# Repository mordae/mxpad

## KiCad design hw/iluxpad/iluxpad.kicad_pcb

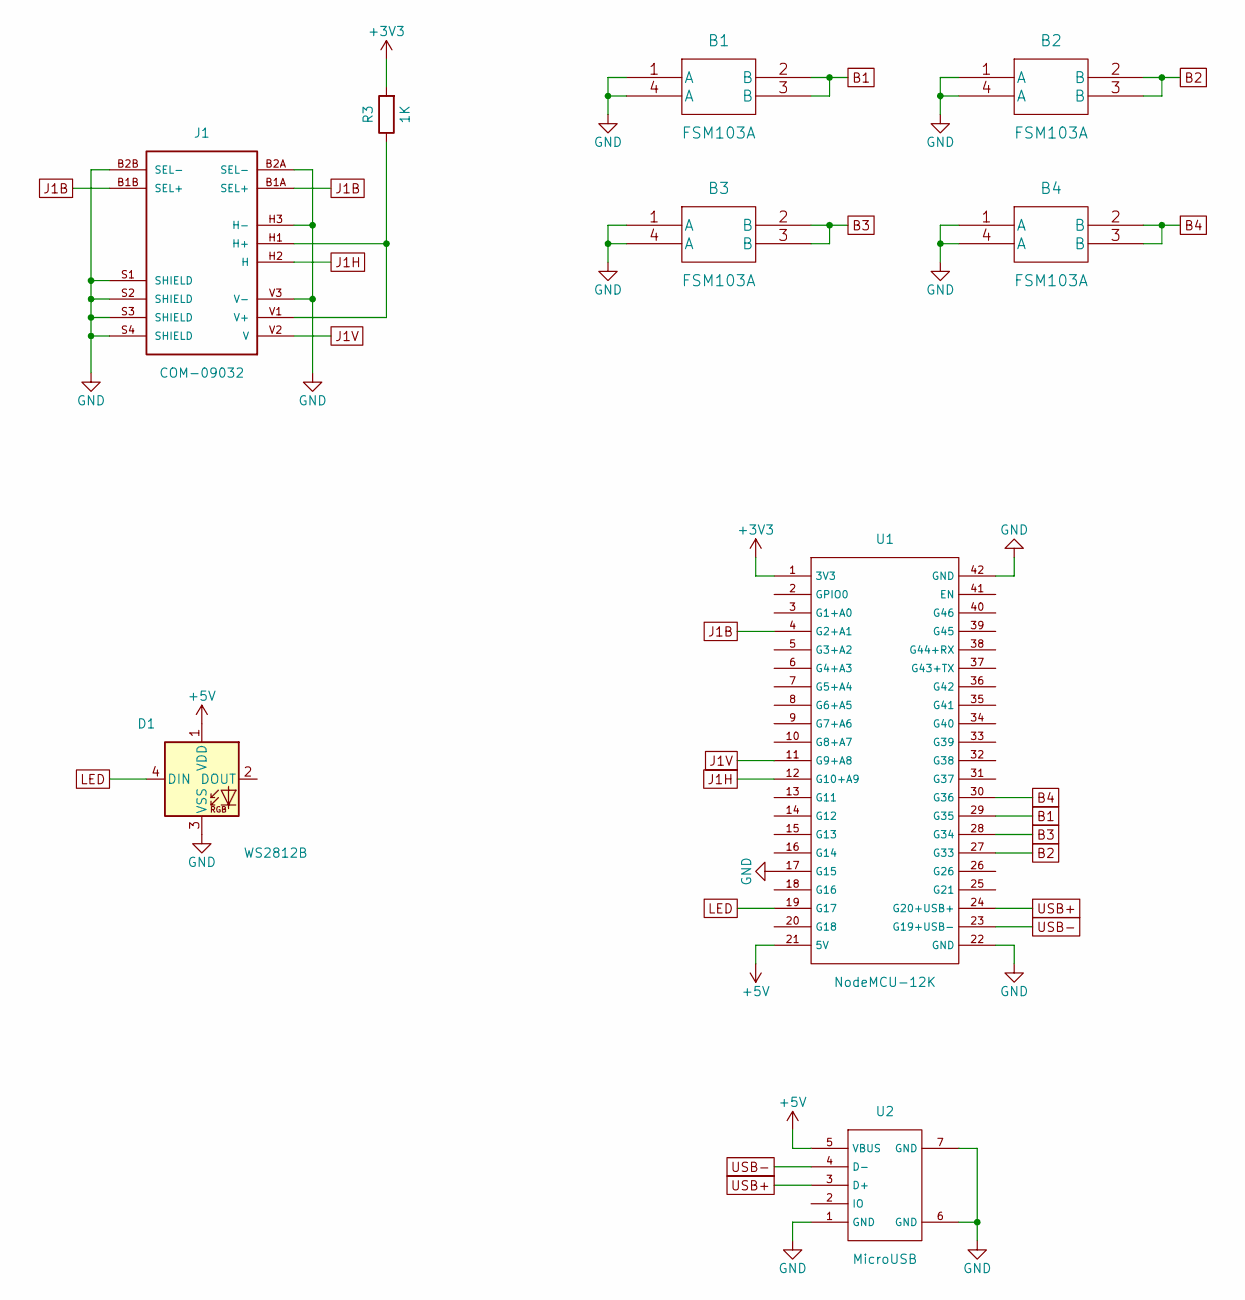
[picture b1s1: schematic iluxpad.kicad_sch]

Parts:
B1, B2, B3, B4: FSM103A; FSM103A-SMD
D1: WS2812B; LED_WS2812B_PLCC4_5.0x5.0mm_P3.2mm
J1: COM-09032; COM-09032-SMD
R3: 1K; R_Axial_DIN0207_L6.3mm_D2.5mm_P10.16mm_Horizontal
U1: NodeMCU-12K; NodeMCU-12K-SMD
U2: MicroUSB

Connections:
+3V3: R3.2, U1.1 (3V3)
+5V: D1.1 (VDD), U1.21 (5V), U2.5 (VBUS)
B1: B1.2 (B), B1.3 (B), U1.29 (G35)
B2: B2.2 (B), B2.3 (B), U1.27 (G33)
B3: B3.2 (B), B3.3 (B), U1.28 (G34)
B4: B4.2 (B), B4.3 (B), U1.30 (G36)
GND: B1.1 (A), B1.4 (A), B2.1 (A), B2.4 (A), B3.1 (A), B3.4 (A), B4.1 (A), B4.4 (A), D1.3 (VSS), J1.B2A (SEL-), J1.B2B (SEL-), J1.H3 (H-), J1.S1 (SHIELD), J1.S2 (SHIELD), J1.S3 (SHIELD), J1.S4 (SHIELD), J1.V3 (V-), U1.17 (G15), U1.22 (GND), U1.42 (GND), U2.1 (GND), U2.6 (GND), U2.7 (GND)
J1B: J1.B1A (SEL+), J1.B1B (SEL+), U1.4 (G2+A1)
J1H: J1.H2 (H), U1.12 (G10+A9)
J1V: J1.V2 (V), U1.11 (G9+A8)
LED: D1.4 (DIN), U1.19 (G17)
unnamed: J1.H1 (H+), J1.V1 (V+), R3.1
USB+: U1.24 (G20+USB+), U2.3 (D+)
USB-: U1.23 (G19+USB-), U2.4 (D-)

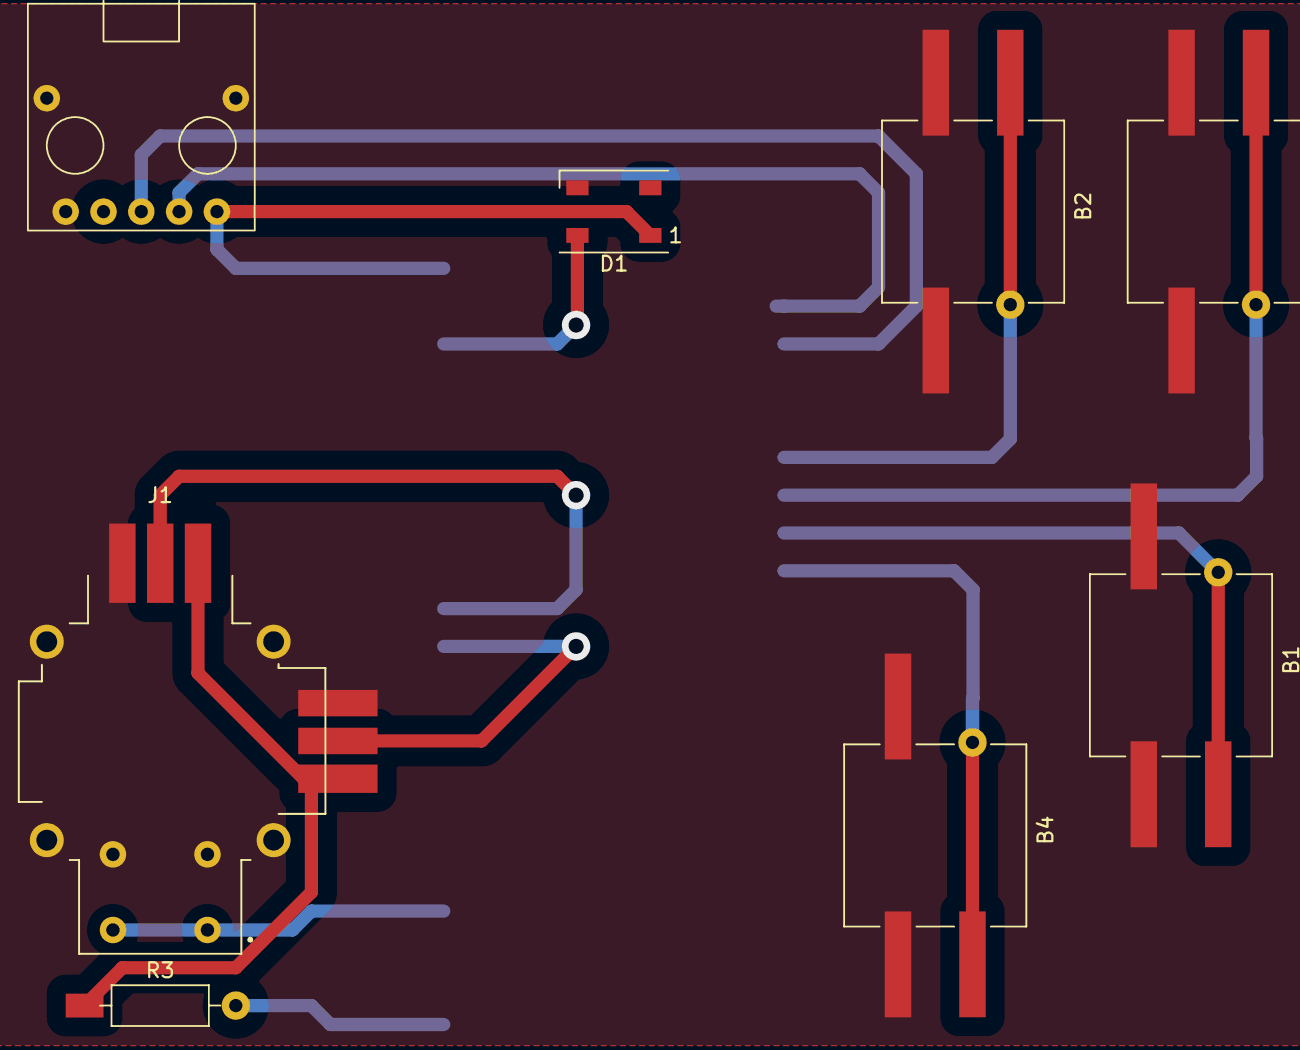
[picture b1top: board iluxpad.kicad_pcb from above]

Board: 2 copper layers, 9 parts (1 on the bottom side), 14 nets.

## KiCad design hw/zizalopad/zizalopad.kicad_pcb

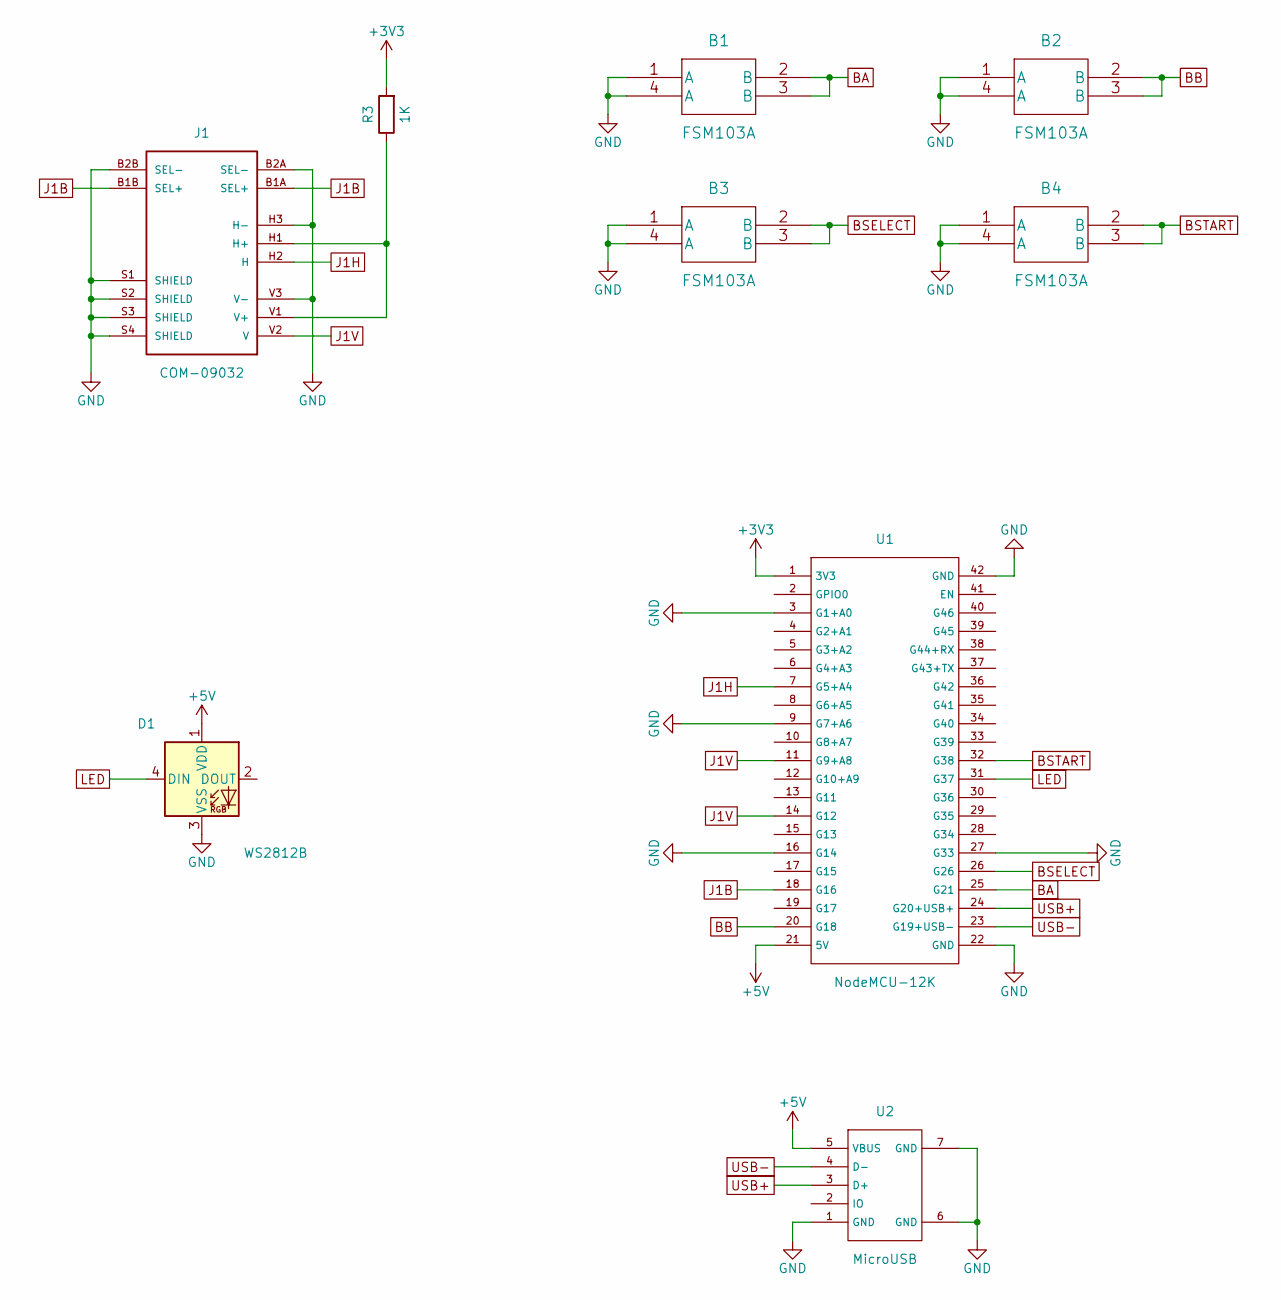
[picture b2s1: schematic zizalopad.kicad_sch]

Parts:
B1, B2, B3, B4: FSM103A; FSM103A-SMD
D1: WS2812B; LED_WS2812B_PLCC4_5.0x5.0mm_P3.2mm
J1: COM-09032; COM-09032-SMD
R3: 1K; R_Axial_DIN0207_L6.3mm_D2.5mm_P7.62mm_Horizontal
U1: NodeMCU-12K; NodeMCU-12K-SMD
U2: MicroUSB

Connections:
+3V3: R3.2, U1.1 (3V3)
+5V: D1.1 (VDD), U1.21 (5V), U2.5 (VBUS)
BA: B1.2 (B), B1.3 (B), U1.25 (G21)
BB: B2.2 (B), B2.3 (B), U1.20 (G18)
BSELECT: B3.2 (B), B3.3 (B), U1.26 (G26)
BSTART: B4.2 (B), B4.3 (B), U1.32 (G38)
GND: B1.1 (A), B1.4 (A), B2.1 (A), B2.4 (A), B3.1 (A), B3.4 (A), B4.1 (A), B4.4 (A), D1.3 (VSS), J1.B2A (SEL-), J1.B2B (SEL-), J1.H3 (H-), J1.S1 (SHIELD), J1.S2 (SHIELD), J1.S3 (SHIELD), J1.S4 (SHIELD), J1.V3 (V-), U1.3 (G1+A0), U1.9 (G7+A6), U1.16 (G14), U1.22 (GND), U1.27 (G33), U1.42 (GND), U2.1 (GND), U2.6 (GND), U2.7 (GND)
J1B: J1.B1A (SEL+), J1.B1B (SEL+), U1.18 (G16)
J1H: J1.H2 (H), U1.7 (G5+A4)
J1V: J1.V2 (V), U1.11 (G9+A8), U1.14 (G12)
LED: D1.4 (DIN), U1.31 (G37)
unnamed: J1.H1 (H+), J1.V1 (V+), R3.1
USB+: U1.24 (G20+USB+), U2.3 (D+)
USB-: U1.23 (G19+USB-), U2.4 (D-)

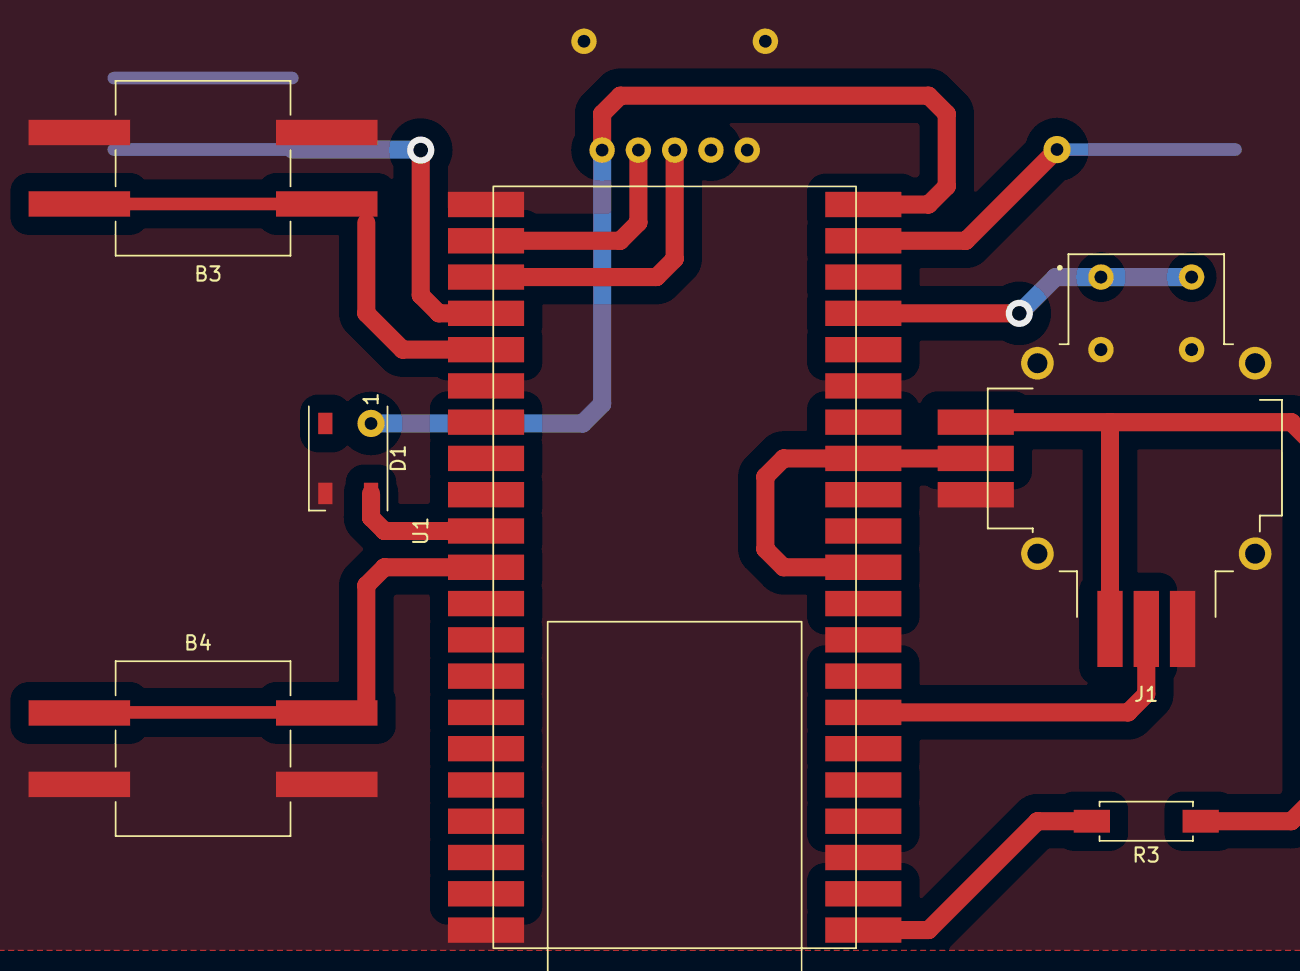
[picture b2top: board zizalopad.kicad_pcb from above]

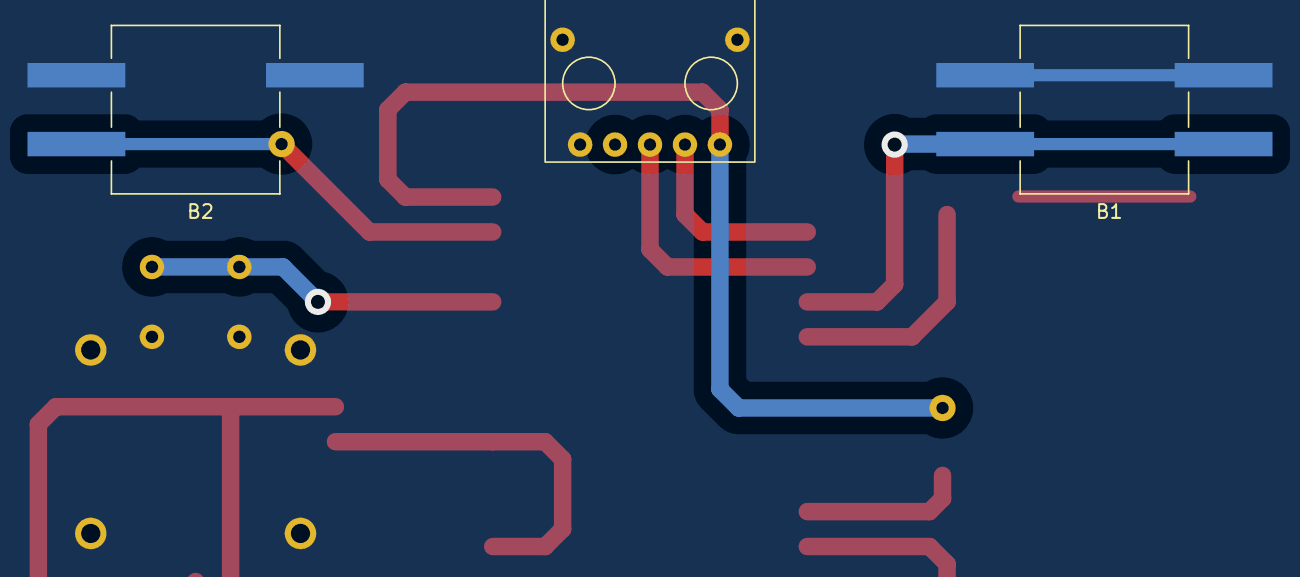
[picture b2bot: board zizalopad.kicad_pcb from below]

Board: 2 copper layers, 9 parts (3 on the bottom side), 14 nets.

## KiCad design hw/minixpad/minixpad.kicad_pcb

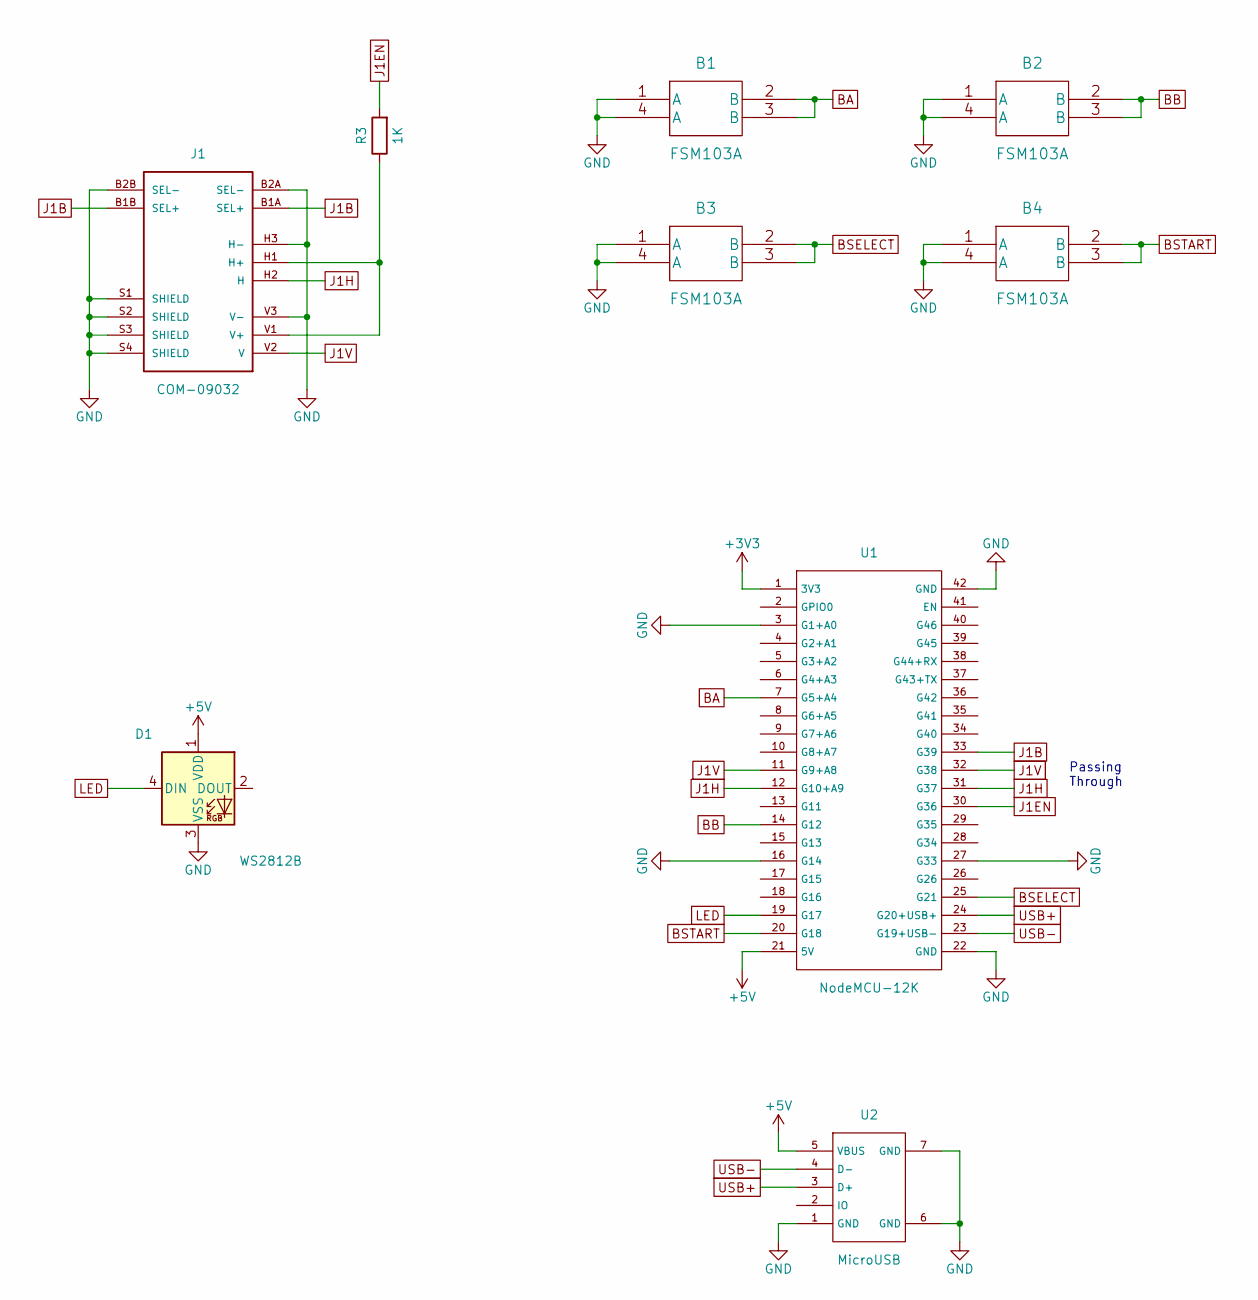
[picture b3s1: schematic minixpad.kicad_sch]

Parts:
B1, B2, B3, B4: FSM103A; FSM103A-SMD
D1: WS2812B; LED_WS2812B_PLCC4_5.0x5.0mm_P3.2mm
J1: COM-09032; COM-09032-SMD
R3: 1K; R_Axial_DIN0204_L3.6mm_D1.6mm_P5.08mm_Horizontal
U1: NodeMCU-12K; NodeMCU-12K-SMD
U2: MicroUSB

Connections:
+3V3: U1.1 (3V3)
+5V: D1.1 (VDD), U1.21 (5V), U2.5 (VBUS)
BA: B1.2 (B), B1.3 (B), U1.7 (G5+A4)
BB: B2.2 (B), B2.3 (B), U1.14 (G12)
BSELECT: B3.2 (B), B3.3 (B), U1.25 (G21)
BSTART: B4.2 (B), B4.3 (B), U1.20 (G18)
GND: B1.1 (A), B1.4 (A), B2.1 (A), B2.4 (A), B3.1 (A), B3.4 (A), B4.1 (A), B4.4 (A), D1.3 (VSS), J1.B2A (SEL-), J1.B2B (SEL-), J1.H3 (H-), J1.S1 (SHIELD), J1.S2 (SHIELD), J1.S3 (SHIELD), J1.S4 (SHIELD), J1.V3 (V-), U1.3 (G1+A0), U1.16 (G14), U1.22 (GND), U1.27 (G33), U1.42 (GND), U2.1 (GND), U2.6 (GND), U2.7 (GND)
J1B: J1.B1A (SEL+), J1.B1B (SEL+), U1.33 (G39)
J1EN: R3.2, U1.30 (G36)
J1H: J1.H2 (H), U1.12 (G10+A9), U1.31 (G37)
J1V: J1.V2 (V), U1.11 (G9+A8), U1.32 (G38)
LED: D1.4 (DIN), U1.19 (G17)
unnamed: J1.H1 (H+), J1.V1 (V+), R3.1
USB+: U1.24 (G20+USB+), U2.3 (D+)
USB-: U1.23 (G19+USB-), U2.4 (D-)

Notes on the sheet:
Passing Through

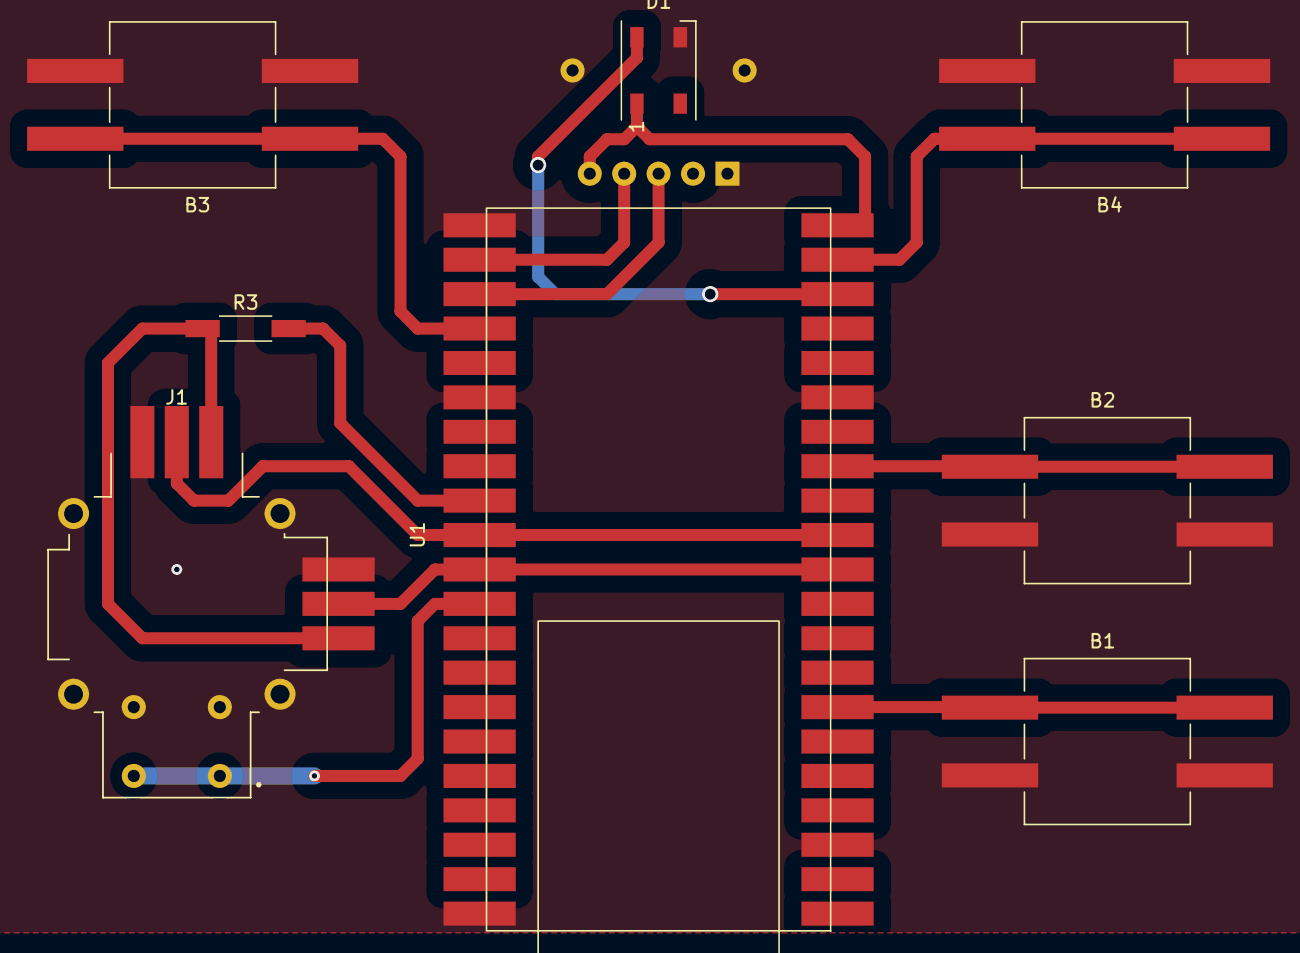
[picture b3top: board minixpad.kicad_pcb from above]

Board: 2 copper layers, 9 parts (1 on the bottom side), 14 nets.

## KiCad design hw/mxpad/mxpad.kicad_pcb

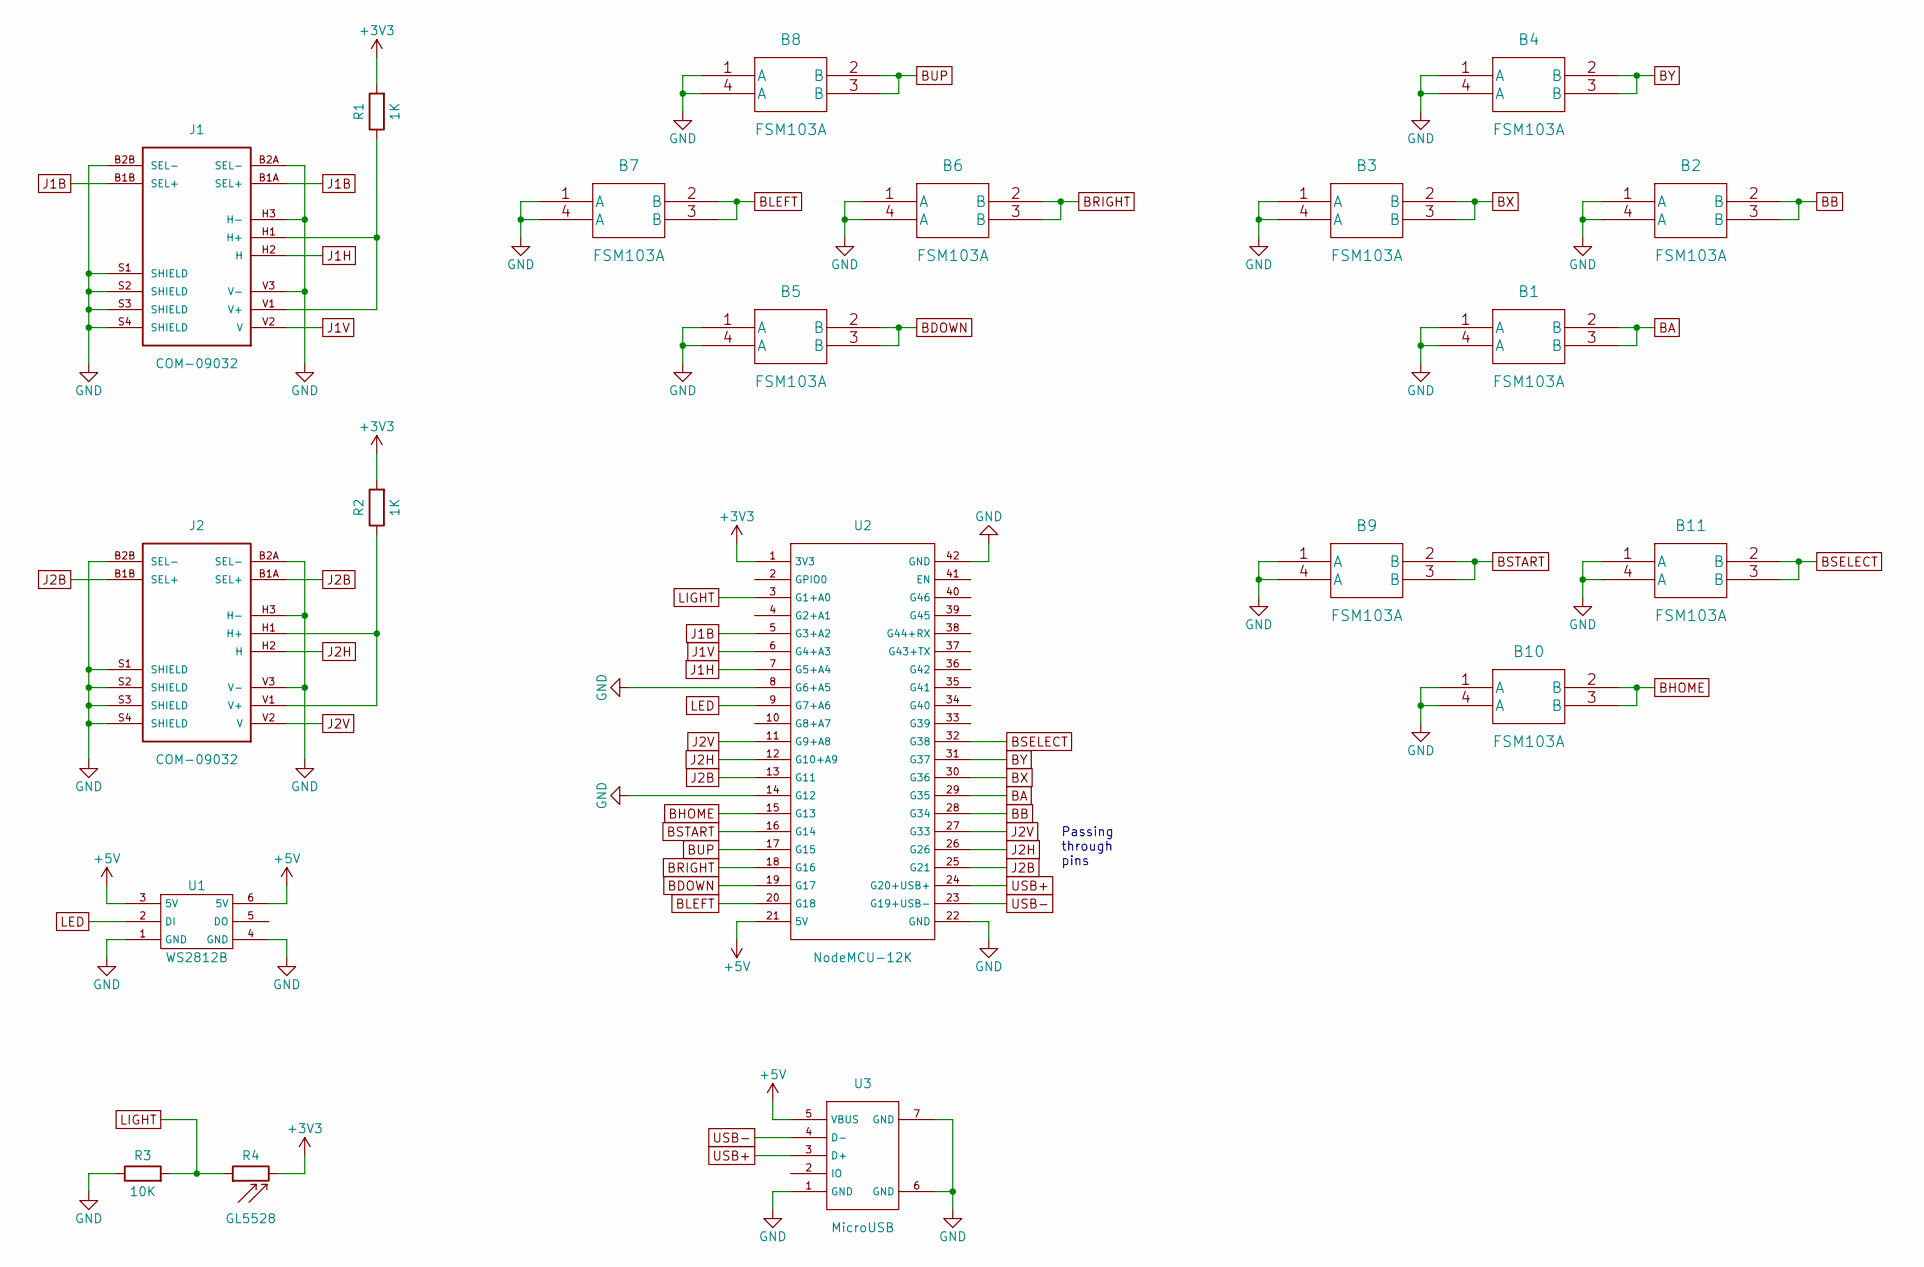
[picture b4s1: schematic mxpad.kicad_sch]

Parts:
B1, B2, B3, B4, B5, B6, B7, B8, B9, B10, B11: FSM103A
J1, J2: COM-09032
R1, R2: 1K; R_Axial_DIN0204_L3.6mm_D1.6mm_P5.08mm_Horizontal
R3: 10K; R_Axial_DIN0204_L3.6mm_D1.6mm_P5.08mm_Horizontal
R4: GL5528; R_LDR_4.9x4.2mm_P2.54mm_Vertical
U1: WS2812B
U2: NodeMCU-12K
U3: MicroUSB

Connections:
+3V3: R1.2, R2.2, R4.2, U2.1 (3V3)
+5V: U1.3 (5V), U1.6 (5V), U2.21 (5V), U3.5 (VBUS)
BA: B1.2 (B), B1.3 (B), U2.29 (GPIO35)
BB: B2.2 (B), B2.3 (B), U2.28 (GPIO34)
BDOWN: B5.2 (B), B5.3 (B), U2.19 (GPIO17)
BHOME: B10.2 (B), B10.3 (B), U2.15 (GPIO13)
BLEFT: B7.2 (B), B7.3 (B), U2.20 (GPIO18)
BRIGHT: B6.2 (B), B6.3 (B), U2.18 (GPIO16)
BSELECT: B11.2 (B), B11.3 (B), U2.32 (GPIO38)
BSTART: B9.2 (B), B9.3 (B), U2.16 (GPIO14)
BUP: B8.2 (B), B8.3 (B), U2.17 (GPIO15)
BX: B3.2 (B), B3.3 (B), U2.30 (GPIO36)
BY: B4.2 (B), B4.3 (B), U2.31 (GPIO37)
GND: B1.1 (A), B1.4 (A), B2.1 (A), B2.4 (A), B3.1 (A), B3.4 (A), B4.1 (A), B4.4 (A), B5.1 (A), B5.4 (A), B6.1 (A), B6.4 (A), B7.1 (A), B7.4 (A), B8.1 (A), B8.4 (A), B9.1 (A), B9.4 (A), B10.1 (A), B10.4 (A), B11.1 (A), B11.4 (A), J1.B2A (SEL-), J1.B2B (SEL-), J1.H3 (H-), J1.S1 (SHIELD), J1.S2 (SHIELD), J1.S3 (SHIELD), J1.S4 (SHIELD), J1.V3 (V-), J2.B2A (SEL-), J2.B2B (SEL-), J2.H3 (H-), J2.S1 (SHIELD), J2.S2 (SHIELD), J2.S3 (SHIELD), J2.S4 (SHIELD), J2.V3 (V-), R3.1, U1.1 (GND), U1.4 (GND), U2.8 (GPIO6), U2.14 (GPIO12), U2.22 (GND), U2.42 (GND), U3.1 (GND), U3.6 (GND), U3.7 (GND)
J1B: J1.B1A (SEL+), J1.B1B (SEL+), U2.5 (GPIO3)
J1H: J1.H2 (H), U2.7 (GPIO5)
J1V: J1.V2 (V), U2.6 (GPIO4)
J2B: J2.B1A (SEL+), J2.B1B (SEL+), U2.13 (GPIO11), U2.25 (GPIO21)
J2H: J2.H2 (H), U2.12 (GPIO10), U2.26 (GPIO26)
J2V: J2.V2 (V), U2.11 (GPIO9), U2.27 (GPIO33)
LED: U1.2 (DI), U2.9 (GPIO7)
LIGHT: R3.2, R4.1, U2.3 (GPIO1)
unnamed: J1.H1 (H+), J1.V1 (V+), R1.1
unnamed: J2.H1 (H+), J2.V1 (V+), R2.1
USB+: U2.24 (GPIO20), U3.3 (D+)
USB-: U2.23 (GPIO19), U3.4 (D-)

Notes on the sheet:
Passing through pins

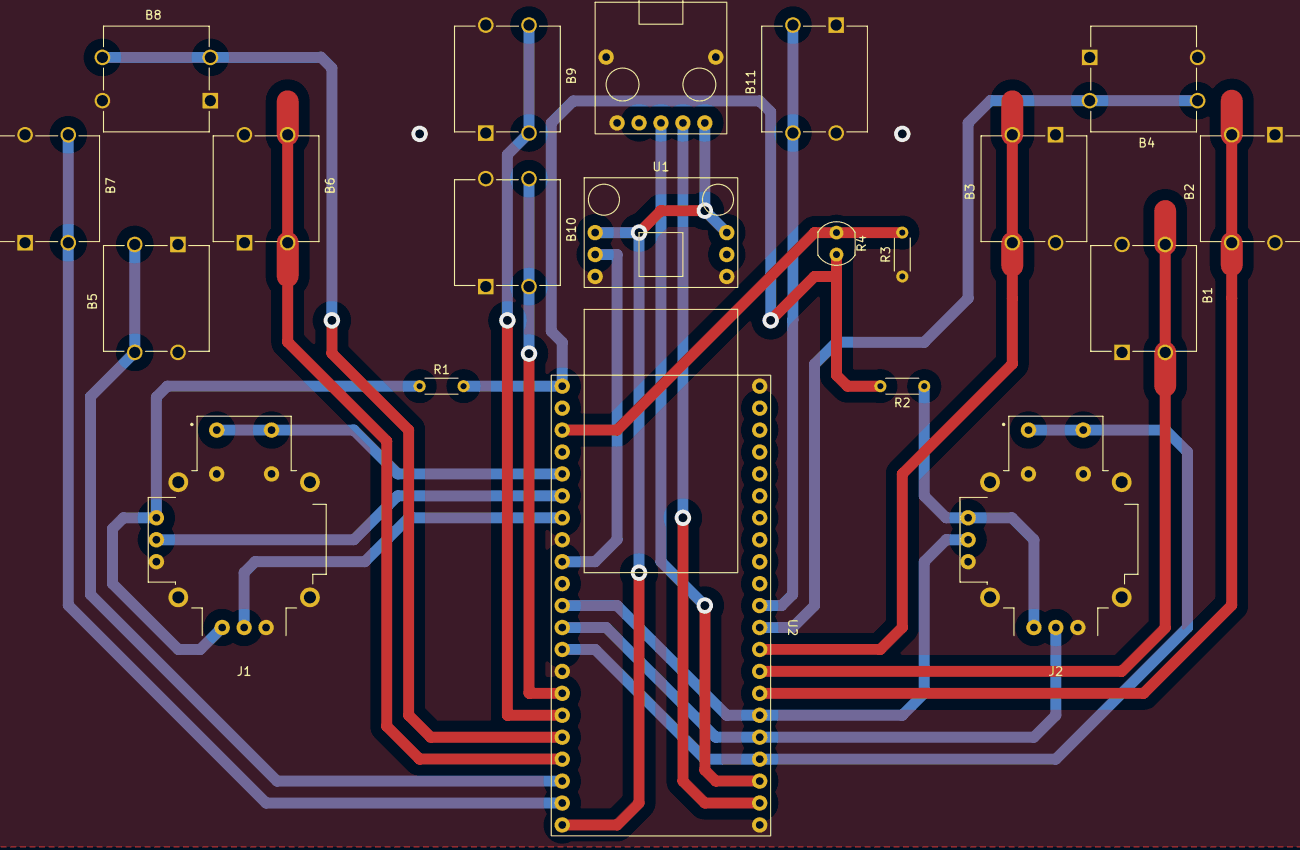
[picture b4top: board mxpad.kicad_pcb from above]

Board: 2 copper layers, 20 parts (0 on the bottom side), 26 nets.

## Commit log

2022-08-03 Initial empty commit
2022-08-03 Add a simple LED rainbow loop
2022-08-03 Add light sensitivity and a single button
2022-08-03 Make Status LED and Light sensor optional
2022-08-08 MXPAD r4 :-)
    USB receive is broken and LED is TBD.
2022-08-08 Fix XInput and LED
2022-08-10 Replace ifdef with if defined
2022-08-10 Improve LED handling and prevent rumble interference
2022-08-10 Fix license
2022-08-13 Design for MiniXPAD
2022-08-13 Add Kconfig for axis inversion
2022-08-13 Make buttons optional
2022-08-13 Add mising parens
2022-08-13 Fix button numbering
2022-08-13 Better ifdefs
2022-08-13 Kconfig for floating pins
    Sometimes we want to route ADC1 pins through some other pins for a good
    layout without involving ADC2. Make it possible to set the unused pins
    to floating.
2022-08-13 Factor ADC1 handling out of main
2022-08-13 Add NVS support
2022-08-13 Initial HID implementation
2022-08-14 Implement 2 HID key maps
2022-08-14 sdkconfig for both device variants
2022-08-14 Fix joysticks without enable pin
2022-08-14 Swap start / select on mxpad
2022-08-14 Use mutexes to protect ADC1 against concurrent access
2022-08-14 Revisit board designs
2022-08-21 Remove fp-info-cache
2022-08-21 Add zizalopad design
2022-08-21 Add ppad design
2022-08-21 Add iluxpad design
2022-08-22 Implement tyrian controls
2022-09-05 Add Raptor layout
